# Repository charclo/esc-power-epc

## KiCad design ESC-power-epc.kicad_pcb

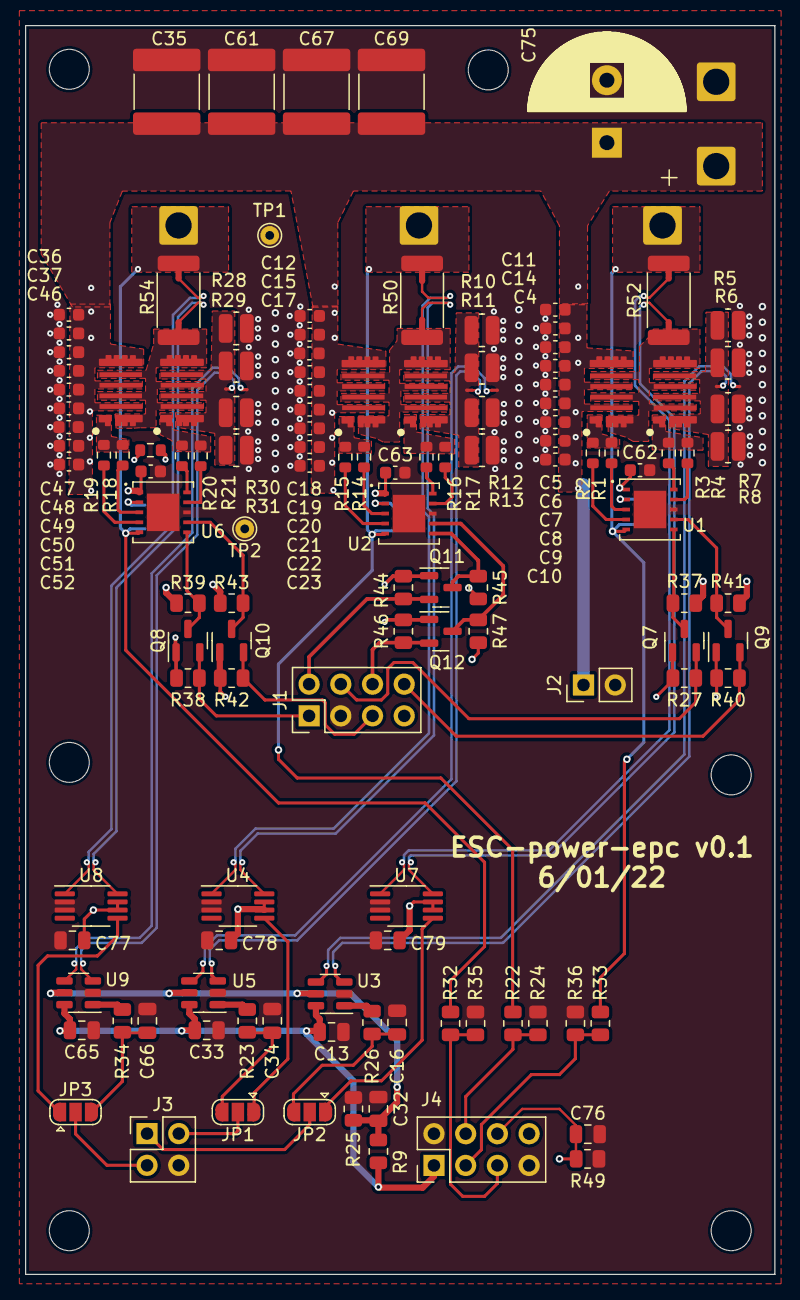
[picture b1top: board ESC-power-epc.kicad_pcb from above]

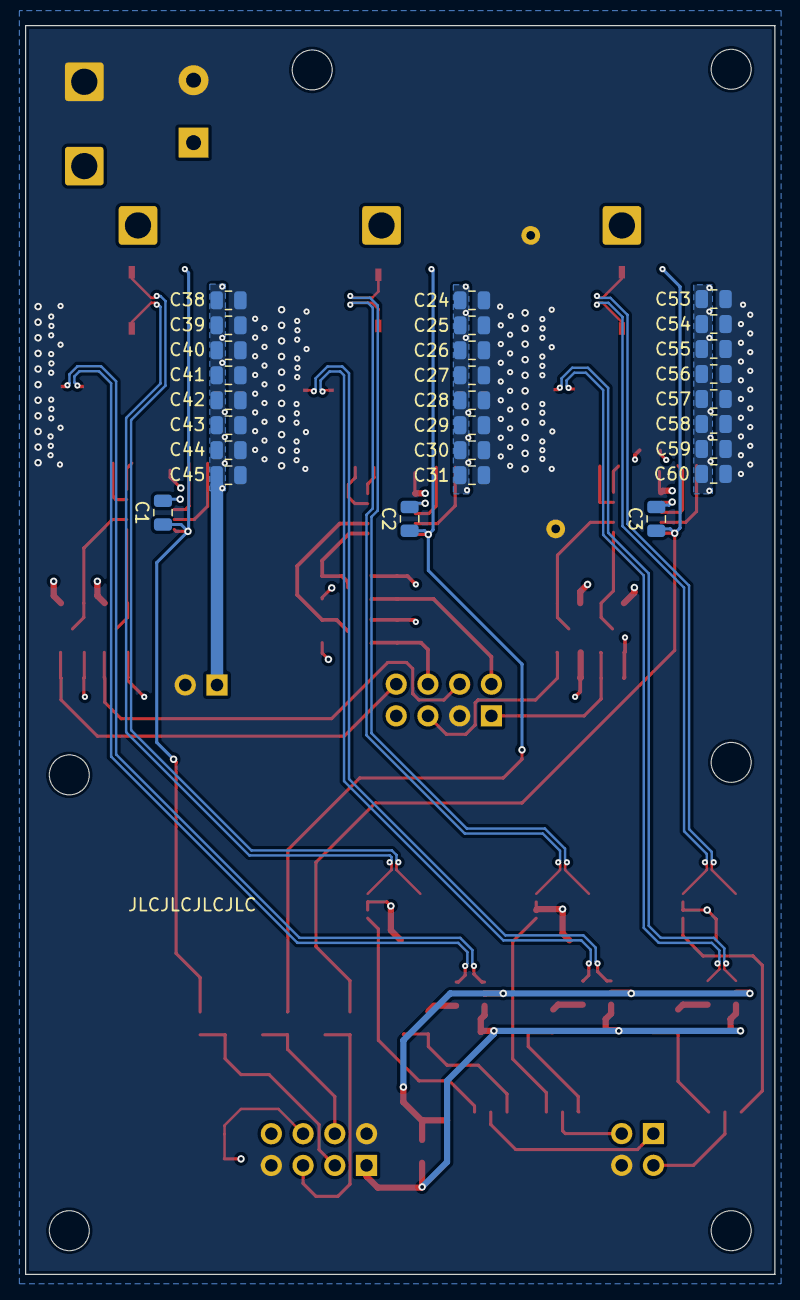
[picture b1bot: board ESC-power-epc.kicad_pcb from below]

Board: 4 copper layers, 60.0 x 100.0 mm, 178 parts (27 on the bottom side), 75 nets.

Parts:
C1, C2, C3: 1u; C_0805_2012Metric
C4, C5, C6, C7, C8, C9, C10, C11, C12, C14, C15, C17, C18, C19, C20, C21, C22, C23, C36, C37, C46, C47, C48, C49, C50, C51, C52: 100n/100V; C_0603_1608Metric
C13, C33, C65: 100n; C_0805_2012Metric
C16, C34, C66: 1n; C_0805_2012Metric
C24, C25, C26, C27, C28, C29, C30, C31, C38, C39, C40, C41, C42, C43, C44, C45, C53, C54, C55, C56, C57, C58, C59, C60: 2.2u/100V; C_0805_2012Metric
C32: 10u; C_0805_2012Metric
C35, C61, C67, C69: 10u/100V; C_2220_5650Metric
C62, C63, C64: 1u; C_0603_1608Metric
C75: 660u; CP_Radial_D12.5mm_P5.00mm
C76, C77, C78, C79: 2u2; C_0805_2012Metric
H1: +; SolderWire-1.5sqmm_1x01_D1.7mm_OD3mm
H2: -; SolderWire-1.5sqmm_1x01_D1.7mm_OD3mm
H3: L1; SolderWire-1.5sqmm_1x01_D1.7mm_OD3mm
H4: L2; SolderWire-1.5sqmm_1x01_D1.7mm_OD3mm
H5: L3; SolderWire-1.5sqmm_1x01_D1.7mm_OD3mm
H6, H7, H8, H9, H10, H11: MountingHole; MountingHole_3.2mm_M3
J1, J4: GATE; PinHeader_2x04_P2.54mm_Vertical
J2: Conn_01x02; PinHeader_1x02_P2.54mm_Vertical
J3: Conn_01x04; PinHeader_2x02_P2.54mm_Vertical
JP1, JP2, JP3: Jumper_3_Bridged12; SolderJumper-3_P1.3mm_Open_RoundedPad1.0x1.5mm
NT1, NT2, NT5, NT6, NT11, NT12: NetTie_2; NetTie-2_SMD_Pad0.26mm
NT3, NT4, NT7, NT8, NT9, NT10: NetTie_2; NetTie-2_SMD_Pad0.5mm
Q1, Q2, Q3, Q4, Q5, Q6: EPC2302
Q7, Q8, Q9, Q10, Q11, Q12: BSS138; SOT-23
R1, R2, R3, R4, R14, R15, R16, R17, R18, R19, R20, R21: 10; R_0603_1608Metric
R5, R6, R7, R8, R10, R11, R12, R13, R28, R29, R30, R31: 2m; 0805W
R9, R25, R27, R37, R38, R39, R40, R41, R42, R43, R44, R45, R46, R47, R49: 10k; R_0805_2012Metric
R22, R32, R33: 39k; R_0805_2012Metric
R23, R26, R34: 1k; R_0805_2012Metric
R24, R35, R36: 2k2; R_0805_2012Metric
R48: NTC 10k; R_0603_1608Metric
R50, R52, R54: 1m; R_2512_6332Metric
TP1, TP2: GND; TestPoint_THTPad_D1.5mm_Drill0.7mm
U1, U2, U6: LM5113SD/NOPB; LM5113SD_NOPB
U3, U5, U9: INA181A2; SOT-23-6
U4, U7, U8: AD8418; MSOP-8_3x3mm_P0.65mm

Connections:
1V65: C32.1, R9.2, R25.1, U3.5 (REF), U5.5 (REF), U9.5 (REF)
+3V3: C13.1, C33.1, C65.1, C77.1, C78.1, C79.1, J4.1, Q7.1 (G), Q8.1 (G), Q9.1 (G), Q10.1 (G), Q11.1 (G), Q12.1 (G), R9.1, R27.1, R38.1, R40.1, R42.1, R44.1, R46.1, R48.1, U3.6 (VS), U4.6 (VS), U4.7 (REF1), U5.6 (VS), U7.6 (VS), U7.7 (REF1), U8.6 (VS), U8.7 (REF1), U9.6 (VS)
+5V: C62.1, C63.1, C64.1, J1.7, R37.1, R39.1, R41.1, R43.1, R45.1, R47.1, U1.1 (VDD), U2.1 (VDD), U6.1 (VDD)
/CURRENT_A: J3.1, JP2.2 (C)
/CURRENT_B: J3.2, JP1.2 (C)
/CURRENT_C: J3.3, JP3.2 (C)
/GaN_A/CUR_SHUNT_LOW: C16.1, JP2.3 (B), R26.2
/GaN_A/CUR_SHUNT_PHASE: JP2.1 (A), U7.5 (OUT)
/GaN_A/GH: Q1.1, R1.2, R2.2
/GaN_A/GL: Q4.1, R3.2, R4.2
/GaN_A/IN+: NT8.1, U7.8 (IN+)
/GaN_A/IN-: NT7.1, U7.1 (IN-)
/GaN_A/S_N: NT2.1, U3.4 (IN-)
/GaN_A/S_P: NT1.1, U3.3 (IN+)
/GaN_B/CUR_SHUNT_LOW: C34.1, JP1.3 (B), R23.2
/GaN_B/CUR_SHUNT_PHASE: JP1.1 (A), U4.5 (OUT)
/GaN_B/GH: Q2.1, R14.2, R15.2
/GaN_B/GL: Q3.1, R16.2, R17.2
/GaN_B/IN+: NT4.1, U4.8 (IN+)
/GaN_B/IN-: NT3.1, U4.1 (IN-)
/GaN_B/S_N: NT6.1, U5.4 (IN-)
/GaN_B/S_P: NT5.1, U5.3 (IN+)
/GaN_C/CUR_SHUNT_LOW: C66.1, JP3.3 (B), R34.2
/GaN_C/CUR_SHUNT_PHASE: JP3.1 (A), U8.5 (OUT)
/GaN_C/GH: Q5.1, R18.2, R19.2
/GaN_C/GL: Q6.1, R20.2, R21.2
/GaN_C/IN+: NT10.1, U8.8 (IN+)
/GaN_C/IN-: NT9.1, U8.1 (IN-)
/GaN_C/S_N: NT12.1, U9.4 (IN-)
/GaN_C/S_P: NT11.1, U9.3 (IN+)
/Gate drivers/H1: J1.4, Q7.2 (S), R27.2
/Gate drivers/H2: J1.2, Q11.2 (S), R44.2
/Gate drivers/H3: J1.1, Q8.2 (S), R38.2
/Gate drivers/L1: J1.8, Q9.2 (S), R40.2
/Gate drivers/L2: J1.6, Q12.2 (S), R46.2
/Gate drivers/L3: J1.5, Q10.2 (S), R42.2
/SENSE_A: J4.3, R33.2, R36.2
/SENSE_B: J4.4, R22.2, R24.2
/SENSE_C: J4.5, R32.2, R35.2
/TEMP_FET: C76.1, J4.6, R48.2, R49.1
/VSA: C1.1, H3.1, NT7.2, R33.1, R52.1, U1.5 (HS)
/VSB: C2.1, H4.1, NT3.2, R22.1, R50.1, U2.5 (HS)
/VSC: C3.1, H5.1, NT9.2, R32.1, R54.1, U6.5 (HS)
GND: C4.2, C5.2, C6.2, C7.2, C8.2, C9.2, C10.2, C11.2, C12.2, C13.2, C14.2, C15.2, C16.2, C17.2, C18.2, C19.2, C20.2, C21.2, C22.2, C23.2, C24.2, C25.2, C26.2, C27.2, C28.2, C29.2, C30.2, C31.2, C32.2, C33.2, C34.2, C35.2, C36.2, C37.2, C38.2, C39.2, C40.2, C41.2, C42.2, C43.2, C44.2, C45.2, C46.2, C47.2, C48.2, C49.2, C50.2, C51.2, C52.2, C53.2, C54.2, C55.2, C56.2, C57.2, C58.2, C59.2, C60.2, C61.2, C62.2, C63.2, C64.2, C65.2, C66.2, C67.2, C69.2, C75.2, C76.2, C77.2, C78.2, C79.2, H2.1, J1.3, J2.2, J3.4, J4.2, J4.7, NT2.2, NT6.2, NT12.2, R5.2, R6.2, R7.2, R8.2, R10.2, R11.2, R12.2, R13.2, R24.1, R25.2, R28.2, R29.2, R30.2, R31.2, R35.1, R36.1, R49.2, TP1.1, TP2.1, U1.8 (VSS), U1.11 (EP), U2.8 (VSS), U2.11 (EP), U3.2 (GND), U4.2 (GND), U4.3 (REF2), U5.2 (GND), U6.8 (VSS), U6.11 (EP), U7.2 (GND), U7.3 (REF2), U8.2 (GND), U8.3 (REF2), U9.2 (GND)
unnamed: C1.2, U1.2 (HB)
unnamed: C2.2, U2.2 (HB)
unnamed: C3.2, U6.2 (HB)
unnamed: NT1.2, Q4.2, Q4.4, Q4.6, R5.1, R6.1, R7.1, R8.1
unnamed: NT4.2, Q2.2, Q2.4, Q2.6, Q3.3, Q3.5, Q3.7, R50.2
unnamed: NT5.2, Q3.2, Q3.4, Q3.6, R10.1, R11.1, R12.1, R13.1
unnamed: NT8.2, Q1.2, Q1.4, Q1.6, Q4.3, Q4.5, Q4.7, R52.2
unnamed: NT10.2, Q5.2, Q5.4, Q5.6, Q6.3, Q6.5, Q6.7, R54.2
unnamed: NT11.2, Q6.2, Q6.4, Q6.6, R28.1, R29.1, R30.1, R31.1
unnamed: Q7.3 (D), R37.2, U1.6 (HI)
unnamed: Q8.3 (D), R39.2, U6.6 (HI)
unnamed: Q9.3 (D), R41.2, U1.7 (LI)
unnamed: Q10.3 (D), R43.2, U6.7 (LI)
unnamed: Q11.3 (D), R45.2, U2.6 (HI)
unnamed: Q12.3 (D), R47.2, U2.7 (LI)
unnamed: R1.1, U1.3 (HOH)
unnamed: R2.1, U1.4 (HOL)
unnamed: R3.1, U1.10 (LOH)
unnamed: R4.1, U1.9 (LOL)
unnamed: R14.1, U2.3 (HOH)
unnamed: R15.1, U2.4 (HOL)
unnamed: R16.1, U2.10 (LOH)
unnamed: R17.1, U2.9 (LOL)
unnamed: R18.1, U6.3 (HOH)
unnamed: R19.1, U6.4 (HOL)
unnamed: R20.1, U6.10 (LOH)
unnamed: R21.1, U6.9 (LOL)
unnamed: R23.1, U5.1 (OUT)
unnamed: R26.1, U3.1 (OUT)
unnamed: R34.1, U9.1 (OUT)
V_SUPPLY: C4.1, C5.1, C6.1, C7.1, C8.1, C9.1, C10.1, C11.1, C12.1, C14.1, C15.1, C17.1, C18.1, C19.1, C20.1, C21.1, C22.1, C23.1, C24.1, C25.1, C26.1, C27.1, C28.1, C29.1, C30.1, C31.1, C35.1, C36.1, C37.1, C38.1, C39.1, C40.1, C41.1, C42.1, C43.1, C44.1, C45.1, C46.1, C47.1, C48.1, C49.1, C50.1, C51.1, C52.1, C53.1, C54.1, C55.1, C56.1, C57.1, C58.1, C59.1, C60.1, C61.1, C67.1, C69.1, C75.1, H1.1, J2.1, Q1.3, Q1.5, Q1.7, Q2.3, Q2.5, Q2.7, Q5.3, Q5.5, Q5.7

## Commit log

2022-12-05 before changing connector
2022-12-09 before meeting
2023-02-20 v0.1

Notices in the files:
parts and their libraries:
Copyright 2021 Accelerated Designs. All rights reserved.
